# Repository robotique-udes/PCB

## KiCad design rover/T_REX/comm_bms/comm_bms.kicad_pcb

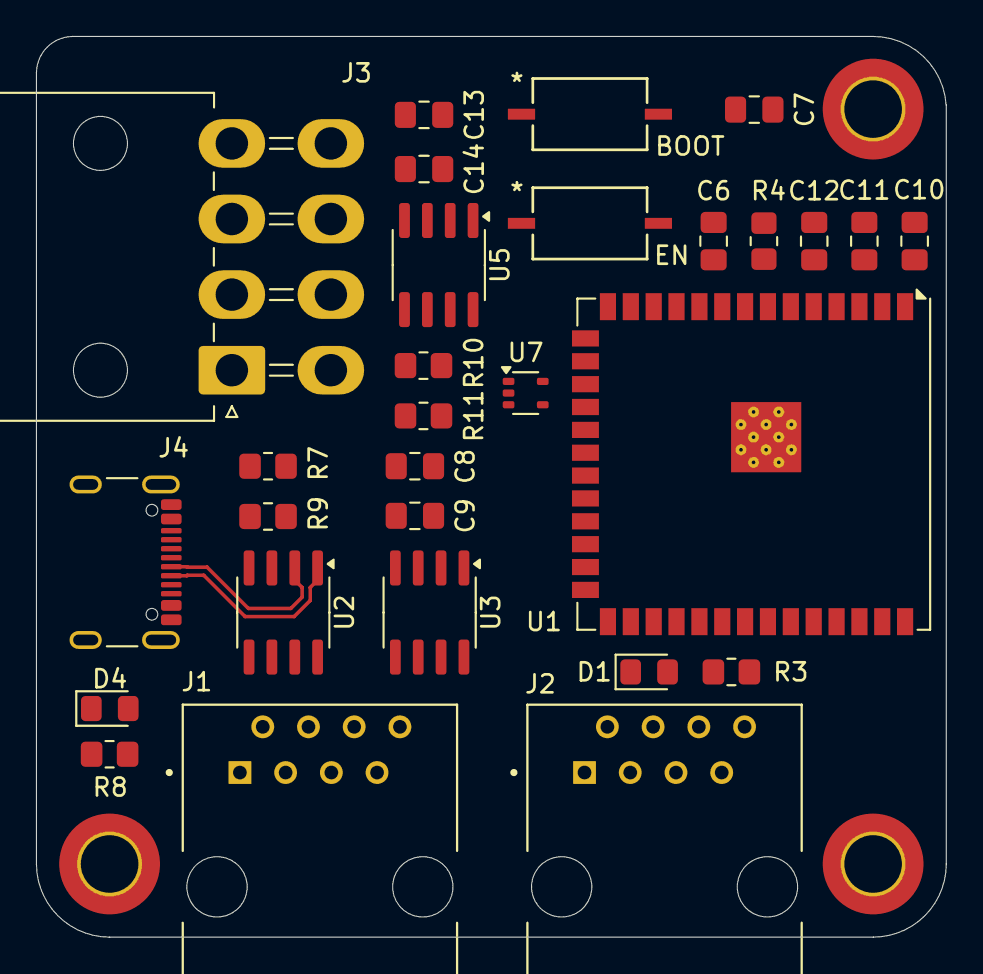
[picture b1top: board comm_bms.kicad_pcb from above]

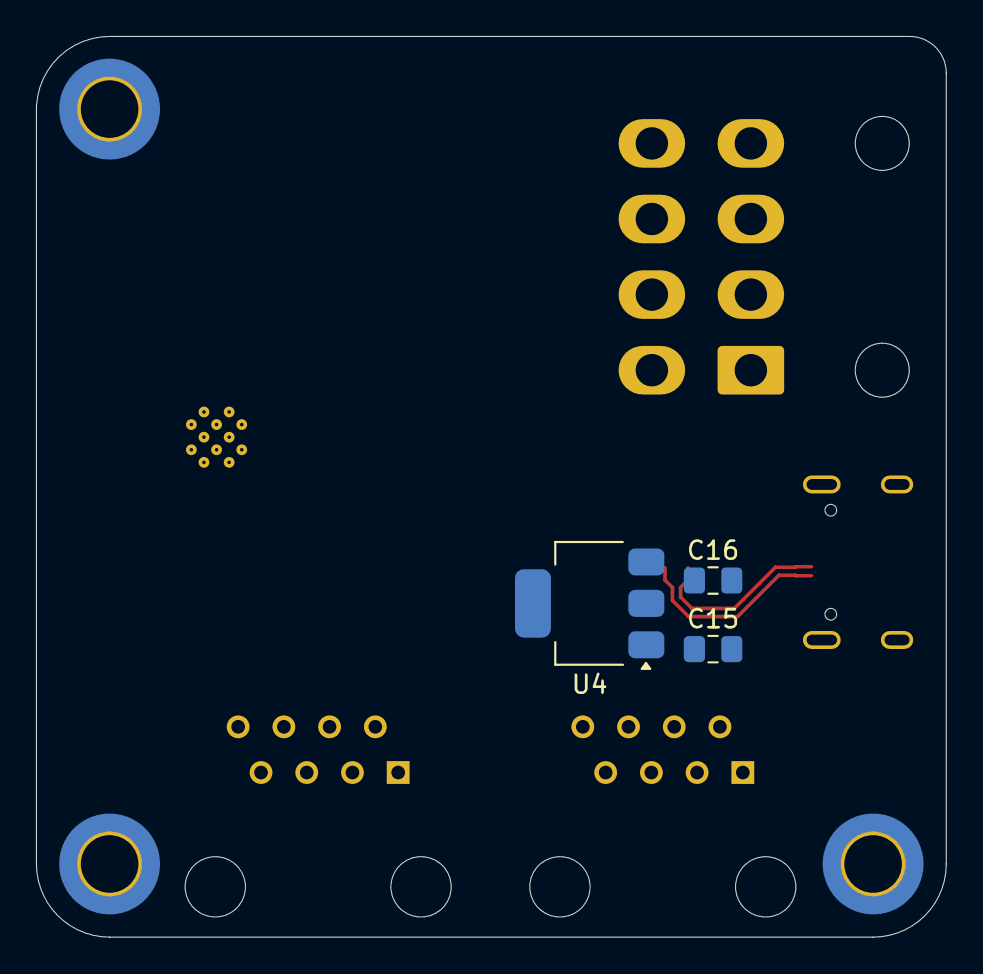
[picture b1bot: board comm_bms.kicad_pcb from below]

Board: 4 copper layers, 50.5 x 50.0 mm, 35 parts (3 on the bottom side), 28 nets.

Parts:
BOOT: TS09-63-25-WT-160-SMT-TR; SW_TS09-63-25_CUD
C6, C7, C9, C11, C14: 100nF; C_0805_2012Metric_Pad1.18x1.45mm_HandSolder
C8, C13, C15: 10uF; C_0805_2012Metric_Pad1.18x1.45mm_HandSolder
C10, C16: 22uF; C_0805_2012Metric_Pad1.18x1.45mm_HandSolder
C12: 1uF; C_0805_2012Metric_Pad1.18x1.45mm_HandSolder
D1: R; LED_0805_2012Metric_Pad1.15x1.40mm_HandSolder
D4: G; LED_0805_2012Metric_Pad1.15x1.40mm_HandSolder
EN: TS09-63-25-WT-160-SMT-TR; SW_TS09-63-25_CUD
H1, H2, H4: MountingHole_Pad; MountingHole_3.2mm_M3_DIN965_Pad_TopBottom
J1, J2: Eth-Horiz-54601-908WPLF; Ethernet_Horizontal
J3: 39301080; Molex_Mini-Fit_Jr_5569-08A2_2x04_P4.20mm_Horizontal
J4: USB_C_USB4105-GF-A; USB_C_Receptacle_GCT_USB4105-xx-A_16P_TopMnt_Horizontal
R3, R8: 1k; R_0805_2012Metric_Pad1.20x1.40mm_HandSolder
R4: 10k; R_0805_2012Metric_Pad1.20x1.40mm_HandSolder
R7, R9: 5k1; R_0805_2012Metric_Pad1.20x1.40mm_HandSolder
R10, R11: 0; R_0805_2012Metric_Pad1.20x1.40mm_HandSolder
U1: ESP32-S3-WROOM-1; ESP32-S3-WROOM-1U
U2: TVS; SOIC-8_3.9x4.9mm_P1.27mm
U3, U5: SN65HVD232Q; SOIC-8_3.9x4.9mm_P1.27mm
U4: LDO-AZ1117CH2-3.3TRG1; SOT-223-3_TabPin2
U7: AXP1T34; SOT-353_SC-70-5

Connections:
5V_USB: J1.5, J1.7, J2.5, J2.7
+3.3V: C8.1, C9.1, C10.1, C11.1, C13.1, C14.1, C16.1, R4.1, R8.2, U1.2 (3V3), U3.3 (VCC), U4.3 (OUTPUT), U5.3 (VCC), U7.5 (Vcco)
+5V_USB: C15.1, J4.A4 (VBUS), J4.A9 (VBUS), J4.B4 (VBUS), J4.B9 (VBUS), R10.1, U2.3, U4.1 (INPUT)
CANH: J1.1 (CANH), J2.1 (CANH), U3.7 (CANH)
CANH_B: J3.1, U5.7 (CANH)
CANL: J1.2 (CANL), J2.2 (CANL), U3.6 (CANL)
CANL_B: J3.2, U5.6 (CANL)
EN_PB: C6.2, C12.1, EN.2, R4.2, U1.3 (EN)
GND: BOOT.1, C6.1, C7.1, C8.2, C9.2, C10.2, C11.2, C12.2, C13.2, C14.2, C15.2, C16.2, D1.1 (K), D4.1 (K), EN.1, H1.1, H2.1, H4.1, J1.6, J1.8, J2.6, J2.8, J3.7, J4.A1 (GND), J4.A12 (GND), J4.B1 (GND), J4.B12 (GND), J4.S1 (SHIELD), R7.2, R9.2, U1.1 (GND), U1.40 (GND), U1.41 (GND), U2.5, U2.6, U2.7, U2.8, U3.2 (GND), U3.8 (S), U4.2 (GND), U5.2 (GND), U5.8 (S), U7.3 (GND)
GPIO_0: BOOT.2, C7.2, U1.27 (IO0-BOOT)
LED_BUILDIN: R3.2, U1.5 (IO5)
unnamed: D1.2 (A), R3.1
unnamed: D4.2 (A), R8.1
unnamed: J1.3, J2.3
unnamed: J1.4, J2.4
unnamed: J4.A5 (CC1), R7.1
unnamed: J4.B5 (CC2), R9.1
unnamed: R11.2, U7.2 (INPUT)
unnamed: R10.2, U7.1 (Vcci)
PWM_3V: U1.33 (IO40), U7.4 (OUTPUT)
PWM_5V: J3.6, R11.1
PWM_EN: J3.8, U1.34 (IO41)
RXB: U1.36 (RXD0), U5.4 (RXD)
RXC: U1.24 (IO47), U3.4 (RXD)
TXB: U1.37 (TXD0), U5.1 (TXD)
TXC: U1.25 (IO48), U3.1 (TXD)
USB_N: J4.A7 (D-), J4.B7 (D-), U1.13 (IO19-USB_N), U2.2
USB_P: J4.A6 (D+), J4.B6 (D+), U1.14 (IO20-USB-P), U2.1

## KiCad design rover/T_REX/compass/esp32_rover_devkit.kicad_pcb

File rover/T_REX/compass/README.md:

# Antenna
PCB servant de module de centrale inertielle et de boussole

Voici les informations concernant le PCB : Compass

## Image du PCB en 3D

## Objectifs:
* Permettre au Rover d'avoir des information sur sa position et son orientation dans l'espace
* 

## Composants principaux:
* ESP32-S3-WROOM-1
* TJA1050T (CAN BUS)
* WT901 (compass)
* Ports Ethernets
* AZ1117ID-3.3 (LDO)
* TVS diodes

## Fonctionnement:
Le MCU peut lire les données de la centrale inertielle et boussole par UART.
Le MCU peut transmettre les informations du senseur par le CAN bus.
Le CAN bus peut passer à travers le circuit, donc un autre circuit peut être branché à la suite de celui-ci.

## PGIO
### Outputs

Name         | GPIO
---          | ---
LED_BUILDIN  | D2
STEPPIN      | D37
DIRPIN       | D38
ENABLEPIN    | D39

### Communication

Name    | GPIO
---     | ---
USBN    | D19
USBP    | D20
SCL     | D21
SDA     | D09
TX_WT   | D13
RX_WT   | D12
TXC     | D48
RXC     | D47

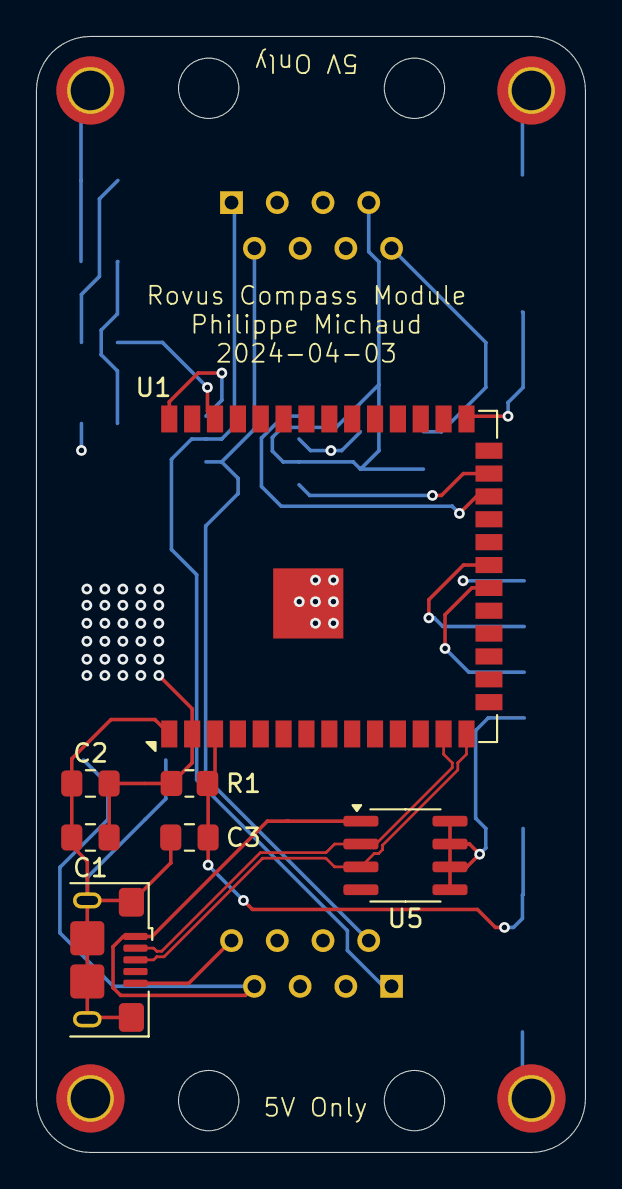
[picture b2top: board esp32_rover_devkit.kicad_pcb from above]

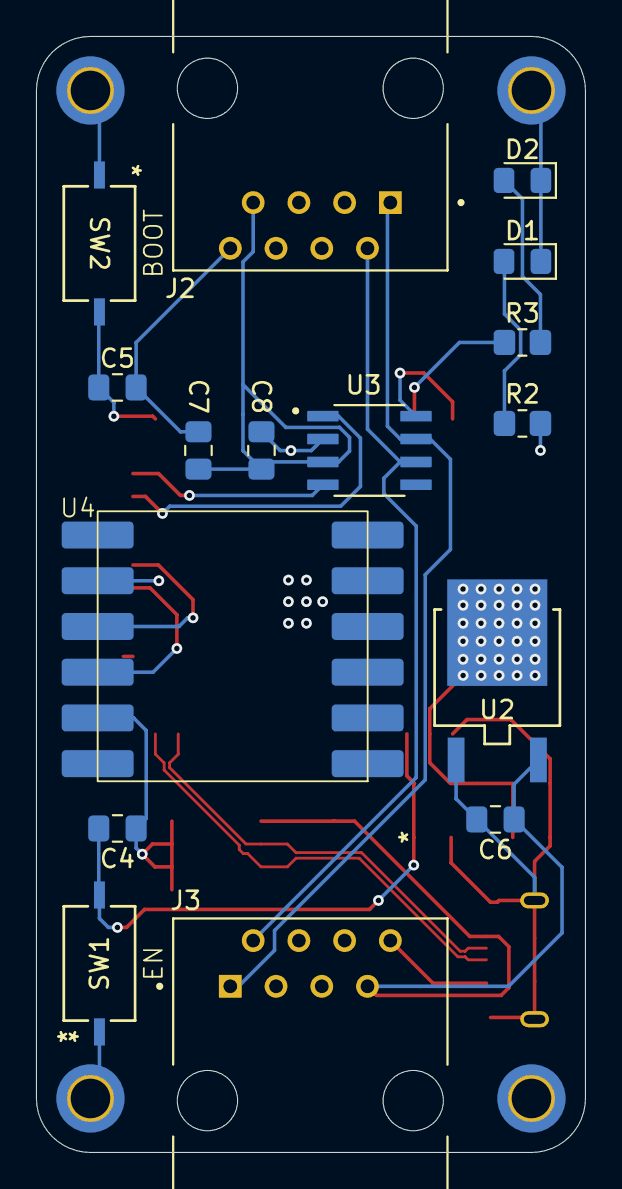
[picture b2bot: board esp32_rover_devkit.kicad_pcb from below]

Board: 4 copper layers, 30.5 x 62.0 mm, 27 parts (16 on the bottom side), 16 nets.

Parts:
C1: 22uF; C_0805_2012Metric_Pad1.18x1.45mm_HandSolder
C2, C4, C5, C8: 100nF; C_0805_2012Metric_Pad1.18x1.45mm_HandSolder
C3: 1uF; C_0805_2012Metric_Pad1.18x1.45mm_HandSolder
C6, C7: 10uF; C_0805_2012Metric_Pad1.18x1.45mm_HandSolder
D1, D2: R; LED_0805_2012Metric_Pad1.15x1.40mm_HandSolder
H1, H2, H3, H4: MountingHole_Pad; MountingHole_2.2mm_M2_DIN965_Pad_TopBottom
J1: USB_B_Micro; USB_Micro-B_Amphenol_10118193-0001LF_Horizontal
J2, J3: RJ45; AMPHENOL_54601-908WPLF
R1: 10K TBV; R_0805_2012Metric_Pad1.20x1.40mm_HandSolder
R2, R3: 1k; R_0805_2012Metric_Pad1.20x1.40mm_HandSolder
SW1, SW2: TS09-63-25-WT-160-SMT-TR; SW_TS09-63-25_CUD
U1: ESP32-S3-WROOM-1
U2: AZ1117ID-3.3TRG1; TO252-2_AZ1117ID-3.3TRG1_DIO
U3: TJA1050T_CM_118; SOIC127P600X175-8N
U4: WT910C
U5: SOIC-8-1EP_3.9x4.9mm_P1.27mm_EP2.29x3mm

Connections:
+3.3V: C1.1, C2.1, R1.1, R2.2, U1.2 (3V3), U2.2 (OUTPUT), U4.2 (Vcc)
+5V: C6.1, C7.1, C8.1, J1.1 (VBUS), J2.7, J3.7, U2.3 (INPUT), U3.3 (VCC), U5.1
CANH: J2.1, J3.1, U3.7 (CANH)
CANL: J2.2, J3.2, U3.6 (CANL)
EN_PB: C3.1, C4.2, R1.2, SW1.2, U1.3 (EN)
GND: C1.2, C2.2, C3.2, C4.1, C5.1, C6.2, C7.2, C8.2, D1.1 (K), D2.1 (K), H1.1, H2.1, H3.1, H4.1, J1.5 (GND), J1.6 (Shield), J2.8, J3.8, SW1.1, SW2.1, U1.1 (GND), U1.40 (GND), U1.41 (GND), U2.1 (GND), U3.2 (GND), U3.8 (S), U4.5 (GND), U5.5, U5.6, U5.7, U5.8
GPIO_0: C5.2, SW2.2, U1.27 (IO0)
LED_BUILDIN: R3.2, U1.38 (IO2)
unnamed: D1.2 (A), R2.1
unnamed: D2.2 (A), R3.1
RX1: U1.20 (IO12), U4.4 (TX)
RXC: U1.24 (IO47), U3.1 (TXD)
TX1: U1.21 (IO13), U4.3 (RX)
TXC: U1.25 (IO48), U3.4 (RXD)
USB_N: J1.2 (D-), U1.13 (IO19), U5.2
USB_P: J1.3 (D+), U1.14 (IO20), U5.3

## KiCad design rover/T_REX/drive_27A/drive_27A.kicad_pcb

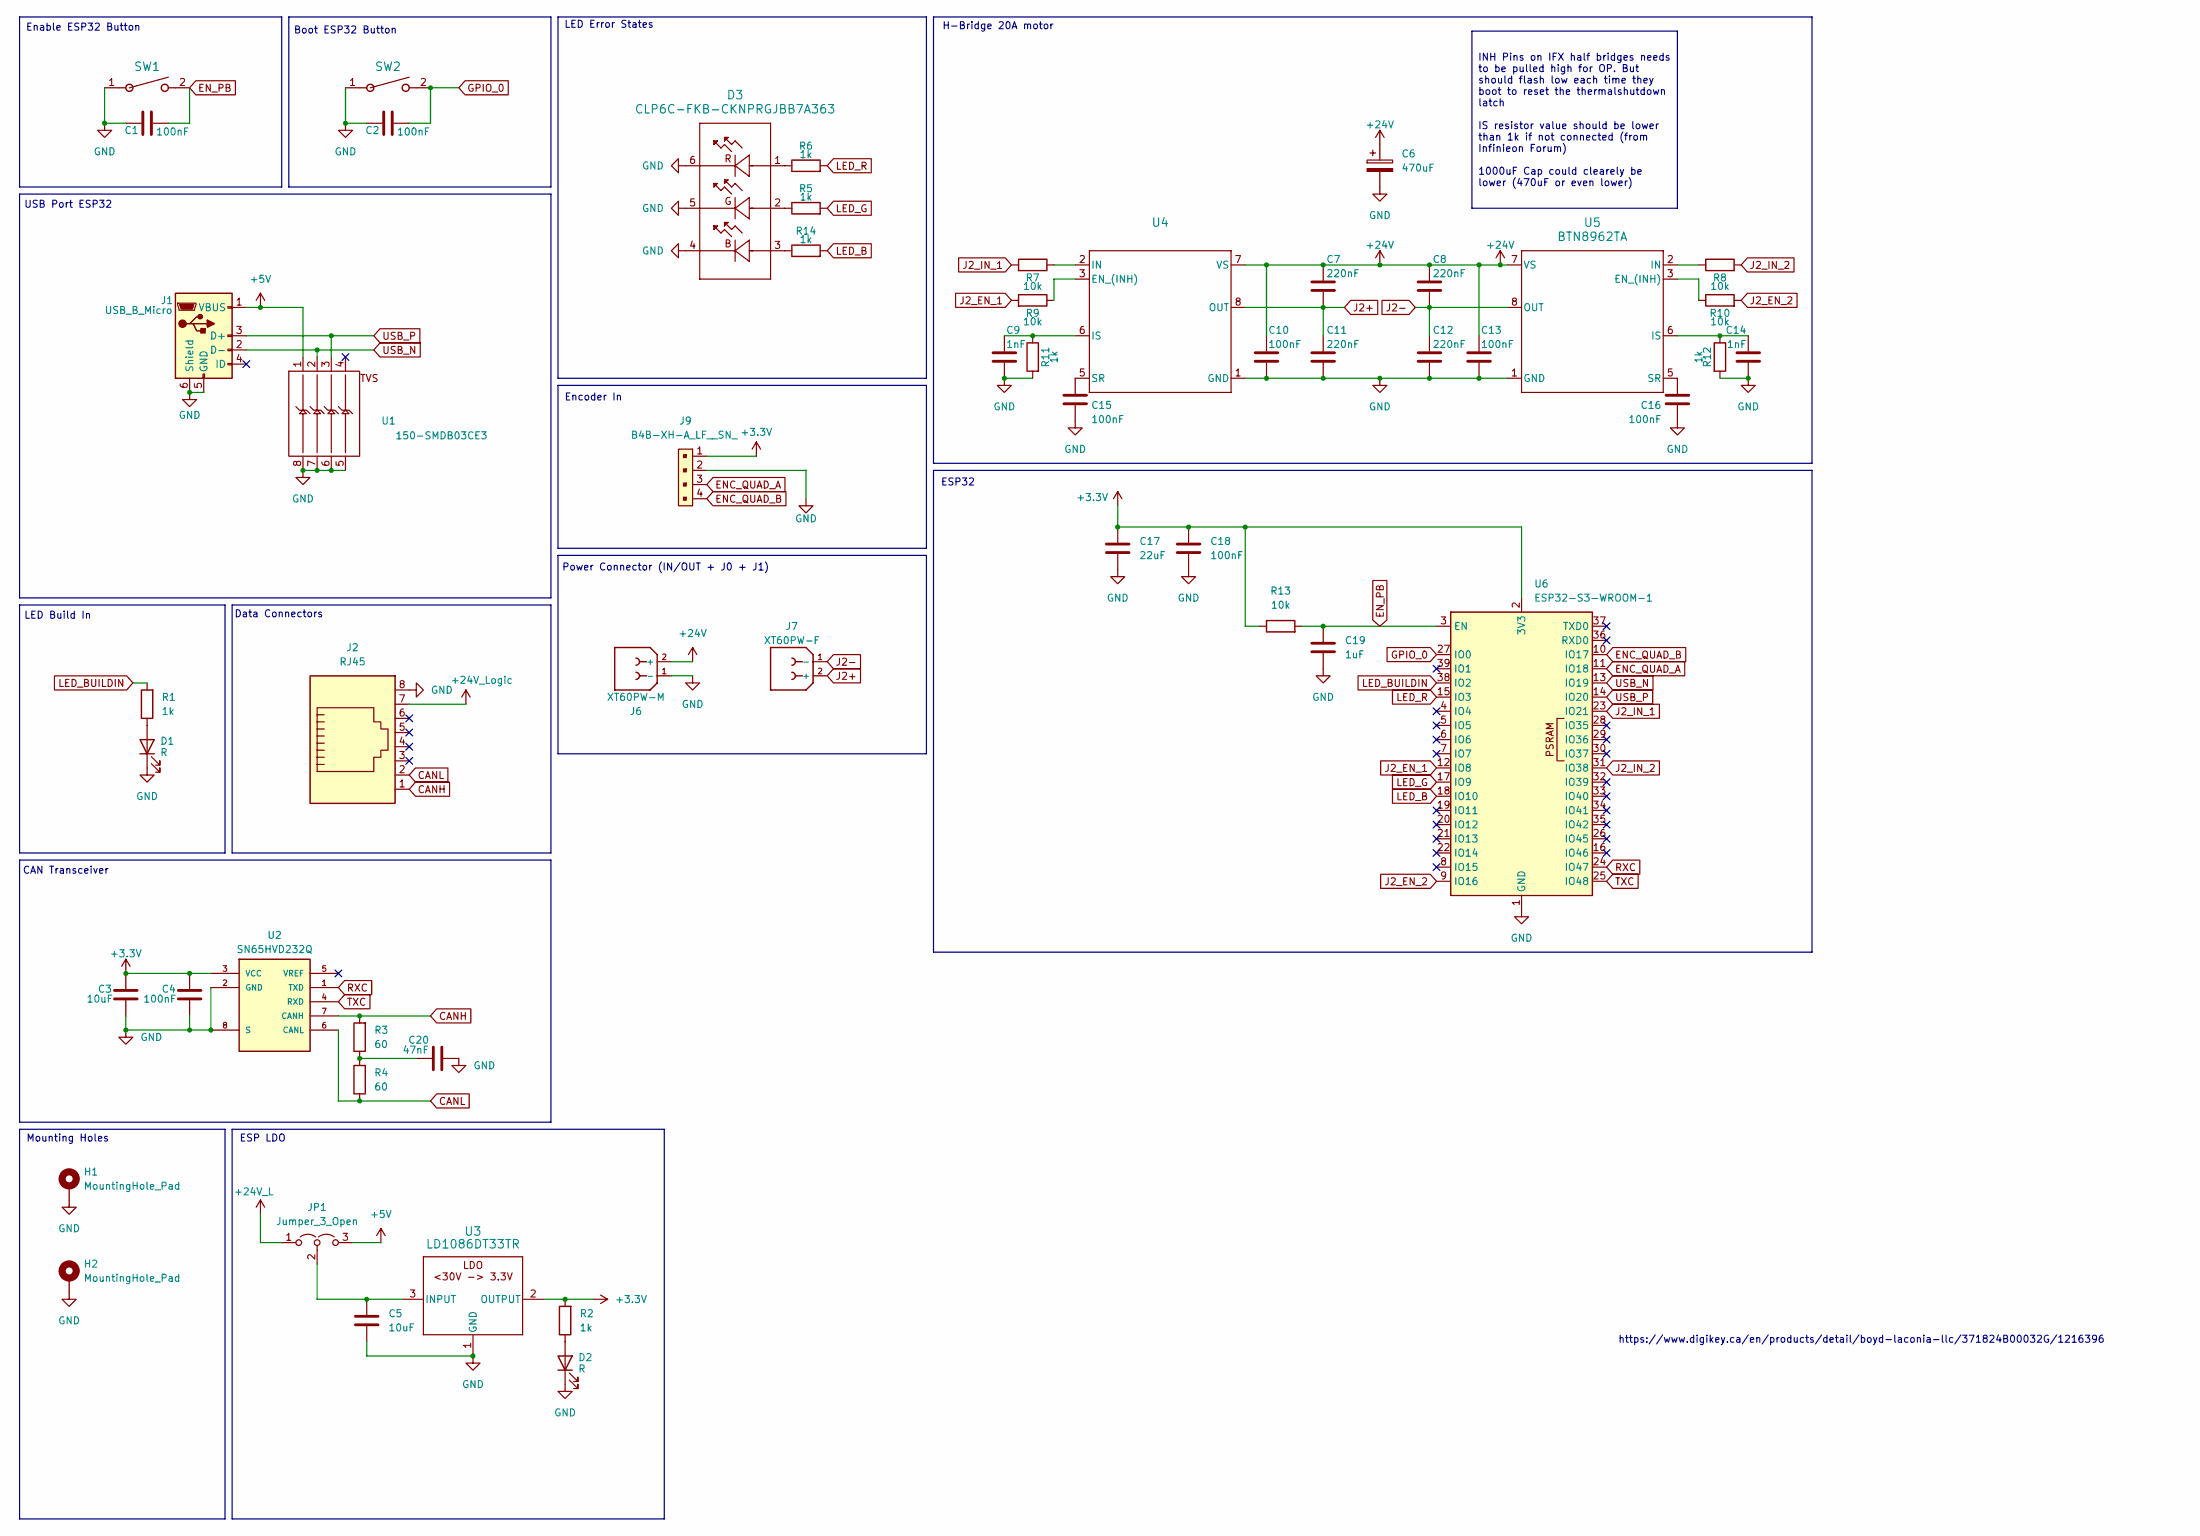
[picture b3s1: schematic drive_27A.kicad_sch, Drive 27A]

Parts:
C1, C2, C4, C10, C13, C15, C16, C18: 100nF; C_0805_2012Metric_Pad1.18x1.45mm_HandSolder; LCSC C111492
C3, C5: 10uF; C_0805_2012Metric_Pad1.18x1.45mm_HandSolder; LCSC C440198
C6: 470uF; CP_Radial_D12.5mm_P5.00mm; LCSC C165494
C7, C8, C11, C12: 220nF; C_0805_2012Metric_Pad1.18x1.45mm_HandSolder; LCSC C86042
C9, C14: 1nF; C_0805_2012Metric_Pad1.18x1.45mm_HandSolder; LCSC C46553
C17: 22uF; C_0805_2012Metric_Pad1.18x1.45mm_HandSolder; LCSC C76634
C19: 1uF; C_0805_2012Metric_Pad1.18x1.45mm_HandSolder; LCSC C77079
C20: 47nF; C_0805_2012Metric_Pad1.18x1.45mm_HandSolder; LCSC C1777
D1, D2: R; LED_0805_2012Metric_Pad1.15x1.40mm_HandSolder; LCSC C19171391
D3: CLP6C-FKB-CKNPRGJBB7A363; CLP6C-FKB-CKNPRGJBB7A363_CRE; LCSC C7107714
H1, H2: MountingHole_Pad; MountingHole_3.2mm_M3_DIN965_Pad_TopBottom
J1: USB_B_Micro; USB_Micro-B_Amphenol_10118193-0001LF_Horizontal; LCSC C132562
J2: RJ45; AMPHENOL_54601-908WPLF; LCSC C598568
J6: XT60PW-M; AMASS_XT60PW-M_1x02_P7.20mm_Horizontal; LCSC C98732
J7: XT60PW-F; AMASS_XT60PW-F_1x02_P7.20mm_Horizontal; LCSC C428722
J9: B4B-XH-A_LF__SN_; JST_PH_B4B-PH-SM4-TB_1x04-1MP_P2.00mm_Vertical; MPN B4B-XH-A(LF)(SN); LCSC C157999
JP1: Jumper_3_Open; PinHeader_1x03_P2.54mm_Vertical
R1, R2, R5, R6, R11, R12, R14: 1k; R_0805_2012Metric_Pad1.20x1.40mm_HandSolder; LCSC C75245
R3, R4: 60; R_0805_2012Metric_Pad1.20x1.40mm_HandSolder; LCSC C2767521
R7, R8, R9, R10, R13: 10k; R_0805_2012Metric_Pad1.20x1.40mm_HandSolder; LCSC C25612
SW1, SW2: TS09-63-25-WT-160-SMT-TR; SW_TS09-63-25_CUD; LCSC C455236
U1: 150-SMDB03CE3; SOIC-8-1EP_3.9x4.9mm_P1.27mm_EP2.29x3mm; LCSC C1973174
U2: SN65HVD232Q; SOIC127P600X175-8N; PARTREV 4; LCSC C130019
U3: LD1086DT33TR; TO252-2_AZ1117ID-3.3TRG1_DIO-L; LCSC C12051
U4, U5: BTN8962TA; PG-TO263-7-1_INF-M; LCSC C534738
U6: ESP32-S3-WROOM-1; LCSC C2980297

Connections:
+3.3V: C3.1, C4.1, C17.1, C18.1, J9.1, R2.2, R13.1, U2.3 (VCC), U3.2 (OUTPUT), U6.2 (3V3)
+5V: J1.1 (VBUS), JP1.3 (B), U1.1
+24V: C6.1, C7.1, C8.1, C10.1, C13.1, J6.2 (+), U4.7 (VS), U5.7 (VS)
CANH: J2.1, R3.2, U2.7 (CANH)
CANL: J2.2, R4.1, U2.6 (CANL)
ENC_QUAD_A: J9.3, U6.11 (IO18)
ENC_QUAD_B: J9.4, U6.10 (IO17)
EN_PB: C1.2, C19.1, R13.2, SW1.2, U6.3 (EN)
GND: C1.1, C2.1, C3.2, C4.2, C5.2, C6.2, C9.2, C10.2, C11.2, C12.2, C13.2, C14.2, C15.2, C16.2, C17.2, C18.2, C19.2, C20.1, D1.1 (K), D2.1 (K), D3.4, D3.5, D3.6, H1.1, H2.1, J1.5 (GND), J1.6 (Shield), J2.8, J6.1 (-), J9.2, R11.2, R12.2, SW1.1, SW2.1, U1.5, U1.6, U1.7, U1.8, U2.2 (GND), U2.8 (S), U3.1 (GND), U4.1 (GND), U5.1 (GND), U6.1 (GND), U6.40 (GND), U6.41 (GND)
GPIO_0: C2.2, SW2.2, U6.27 (IO0)
J2+: C7.2, C11.1, J7.2 (+), U4.8 (OUT)
J2-: C8.2, C12.1, J7.1 (-), U5.8 (OUT)
J2_EN_1: R9.2, U6.12 (IO8)
J2_EN_2: R10.2, U6.9 (IO16)
J2_IN_1: R7.2, U6.23 (IO21)
J2_IN_2: R8.2, U6.31 (IO38)
LED_B: R14.2, U6.18 (IO10)
LED_BUILDIN: R1.2, U6.38 (IO2)
LED_G: R5.2, U6.17 (IO9)
LED_R: R6.2, U6.15 (IO3)
unnamed: C20.2, R3.1, R4.2
unnamed: D1.2 (A), R1.1
unnamed: D2.2 (A), R2.1
unnamed: D3.1, R6.1
unnamed: D3.2, R5.1
unnamed: D3.3, R14.1
unnamed: C5.1, JP1.2 (C), U3.3 (INPUT)
unnamed: R9.1, U4.3 (EN_(INH))
unnamed: R7.1, U4.2 (IN)
unnamed: C9.1, R11.1, U4.6 (IS)
unnamed: C15.1, U4.5 (SR)
unnamed: R10.1, U5.3 (EN_(INH))
unnamed: R8.1, U5.2 (IN)
unnamed: C14.1, R12.1, U5.6 (IS)
unnamed: C16.1, U5.5 (SR)
RXC: U2.1 (TXD), U6.24 (IO47)
TXC: U2.4 (RXD), U6.25 (IO48)
USB_N: J1.2 (D-), U1.2, U6.13 (IO19)
USB_P: J1.3 (D+), U1.3, U6.14 (IO20)

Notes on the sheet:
INH Pins on IFX half bridges needs to be pulled high for OP. But should flash low each time they boot to reset the thermalshutdown latch IS resistor value should be lower than 1k if not connected (from Infinieon Forum) 1000uF Cap could clearely be lower (470uF or even lower)
Boot ESP32 Button
LED Build In
Enable ESP32 Button
CAN Transceiver
Encoder In
LED Error States
Power Connector (IN/OUT + J0 + J1)
ESP LDO
Data Connectors
H-Bridge 20A motor
Mounting Holes
USB Port ESP32
https://www.digikey.ca/en/products/detail/boyd-laconia-llc/371824B00032G/1216396
ESP32

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
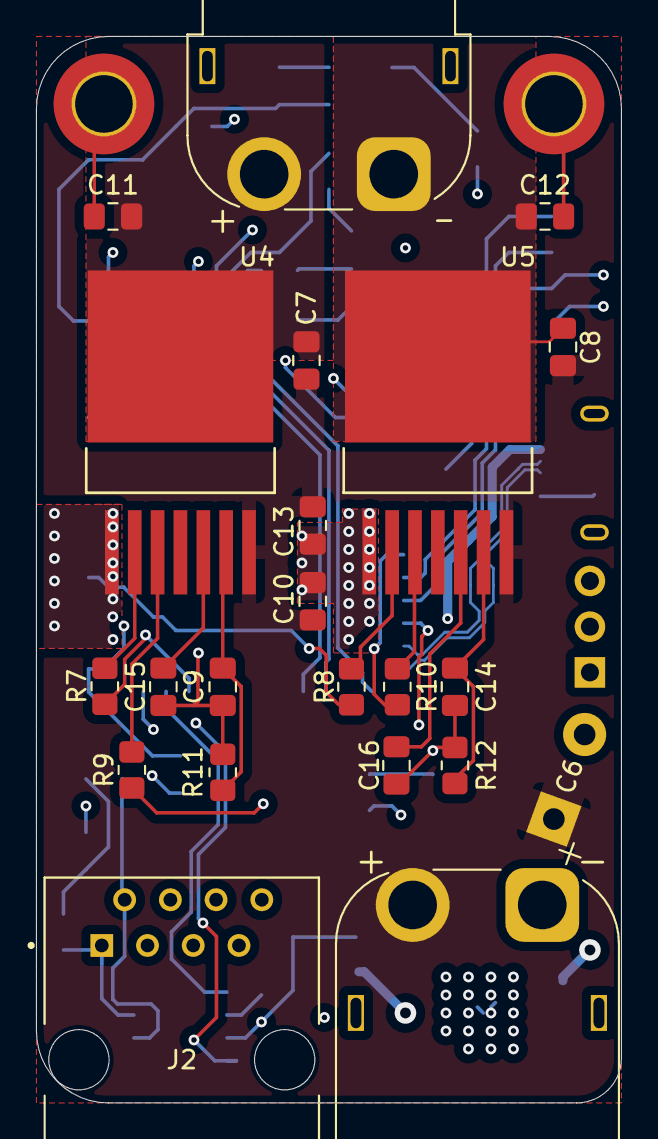
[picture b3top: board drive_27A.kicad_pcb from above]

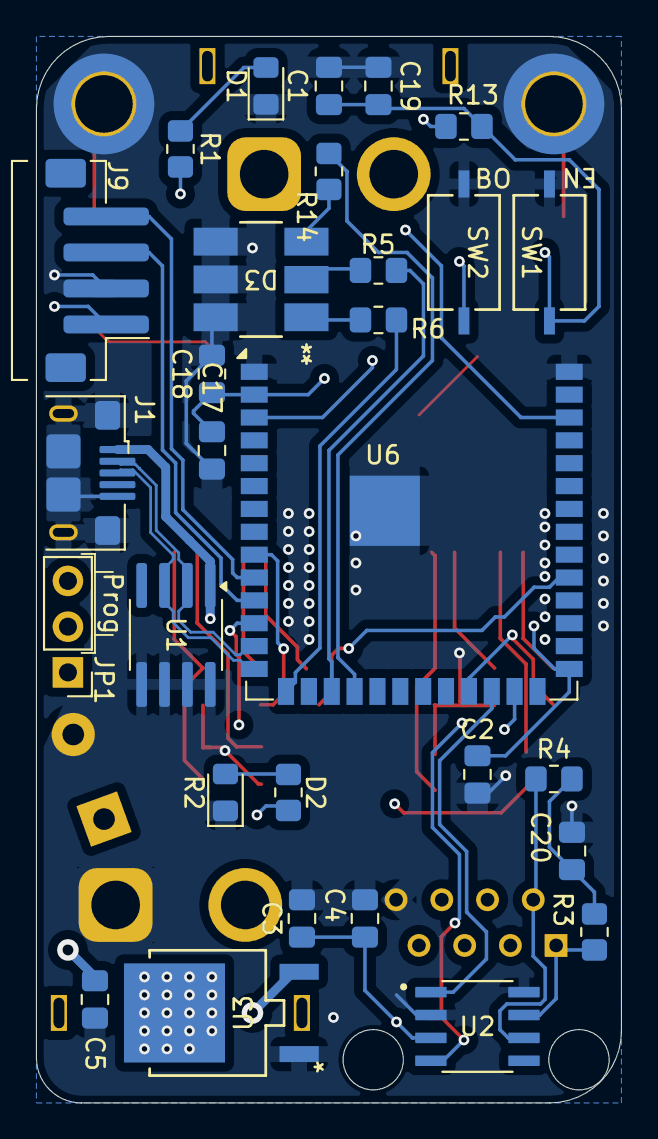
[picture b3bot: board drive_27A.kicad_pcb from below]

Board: 4 copper layers, 32.5 x 59.3 mm, 53 parts (29 on the bottom side), 40 nets.

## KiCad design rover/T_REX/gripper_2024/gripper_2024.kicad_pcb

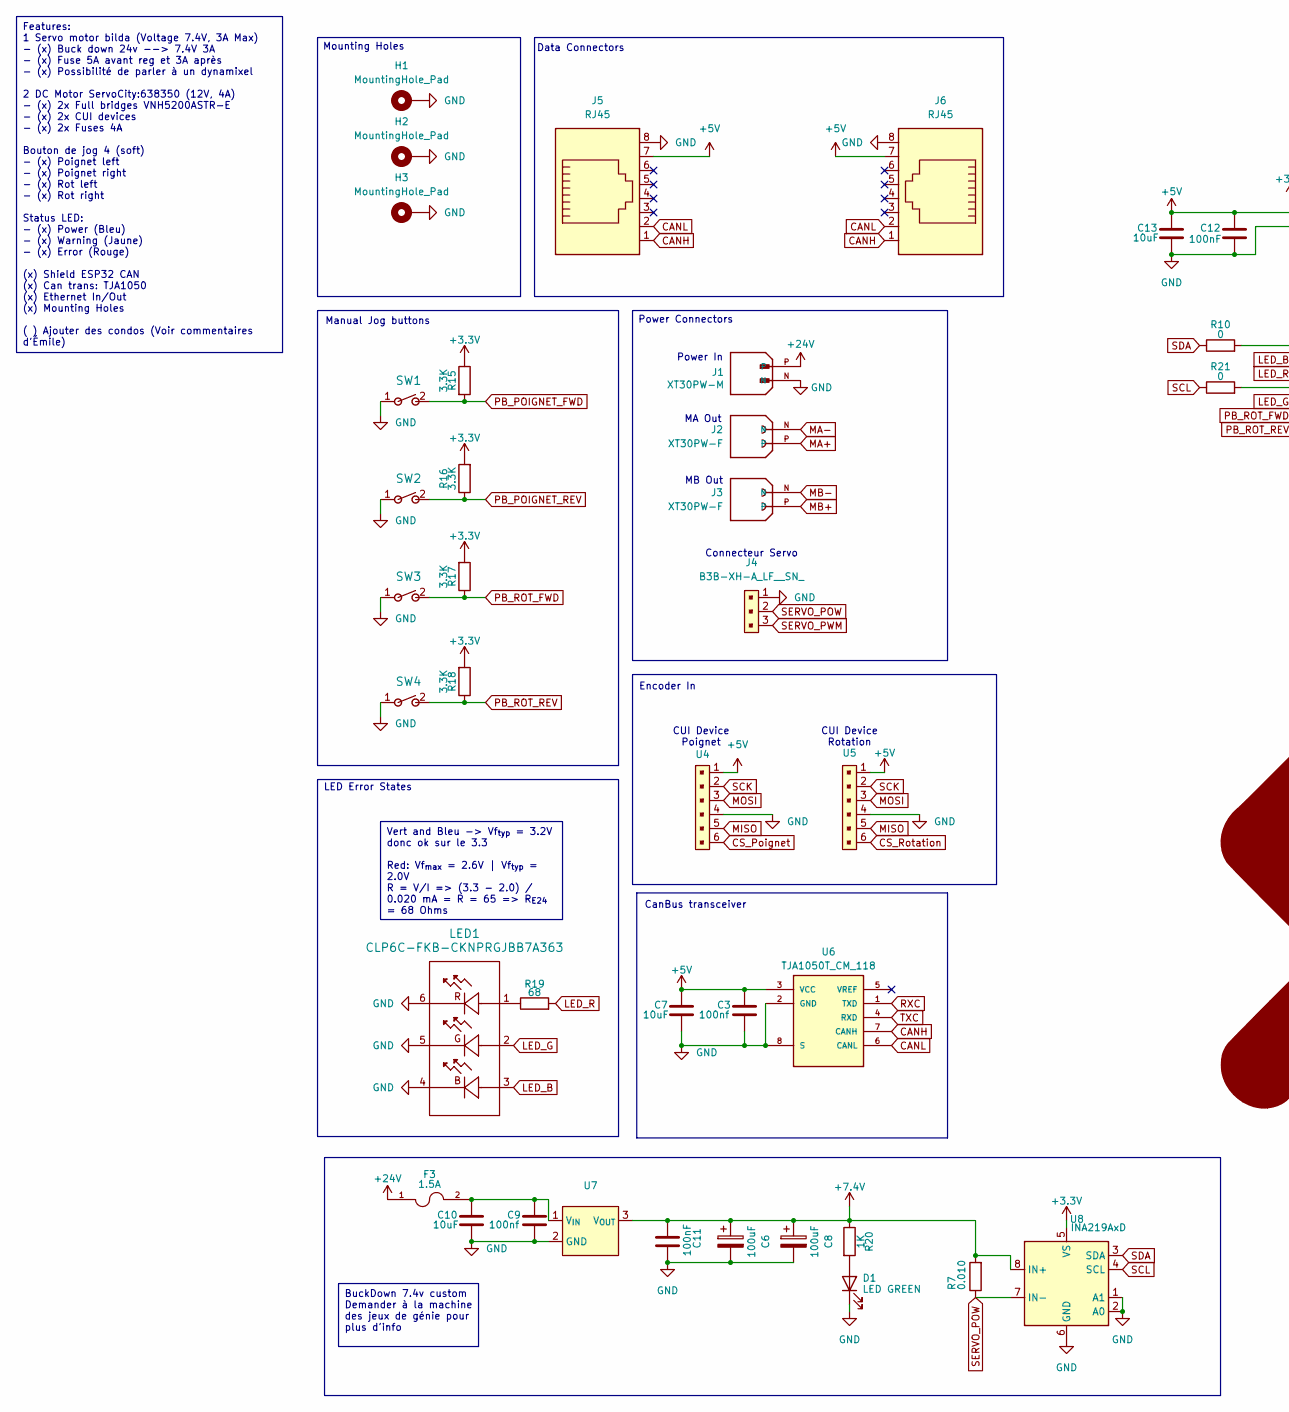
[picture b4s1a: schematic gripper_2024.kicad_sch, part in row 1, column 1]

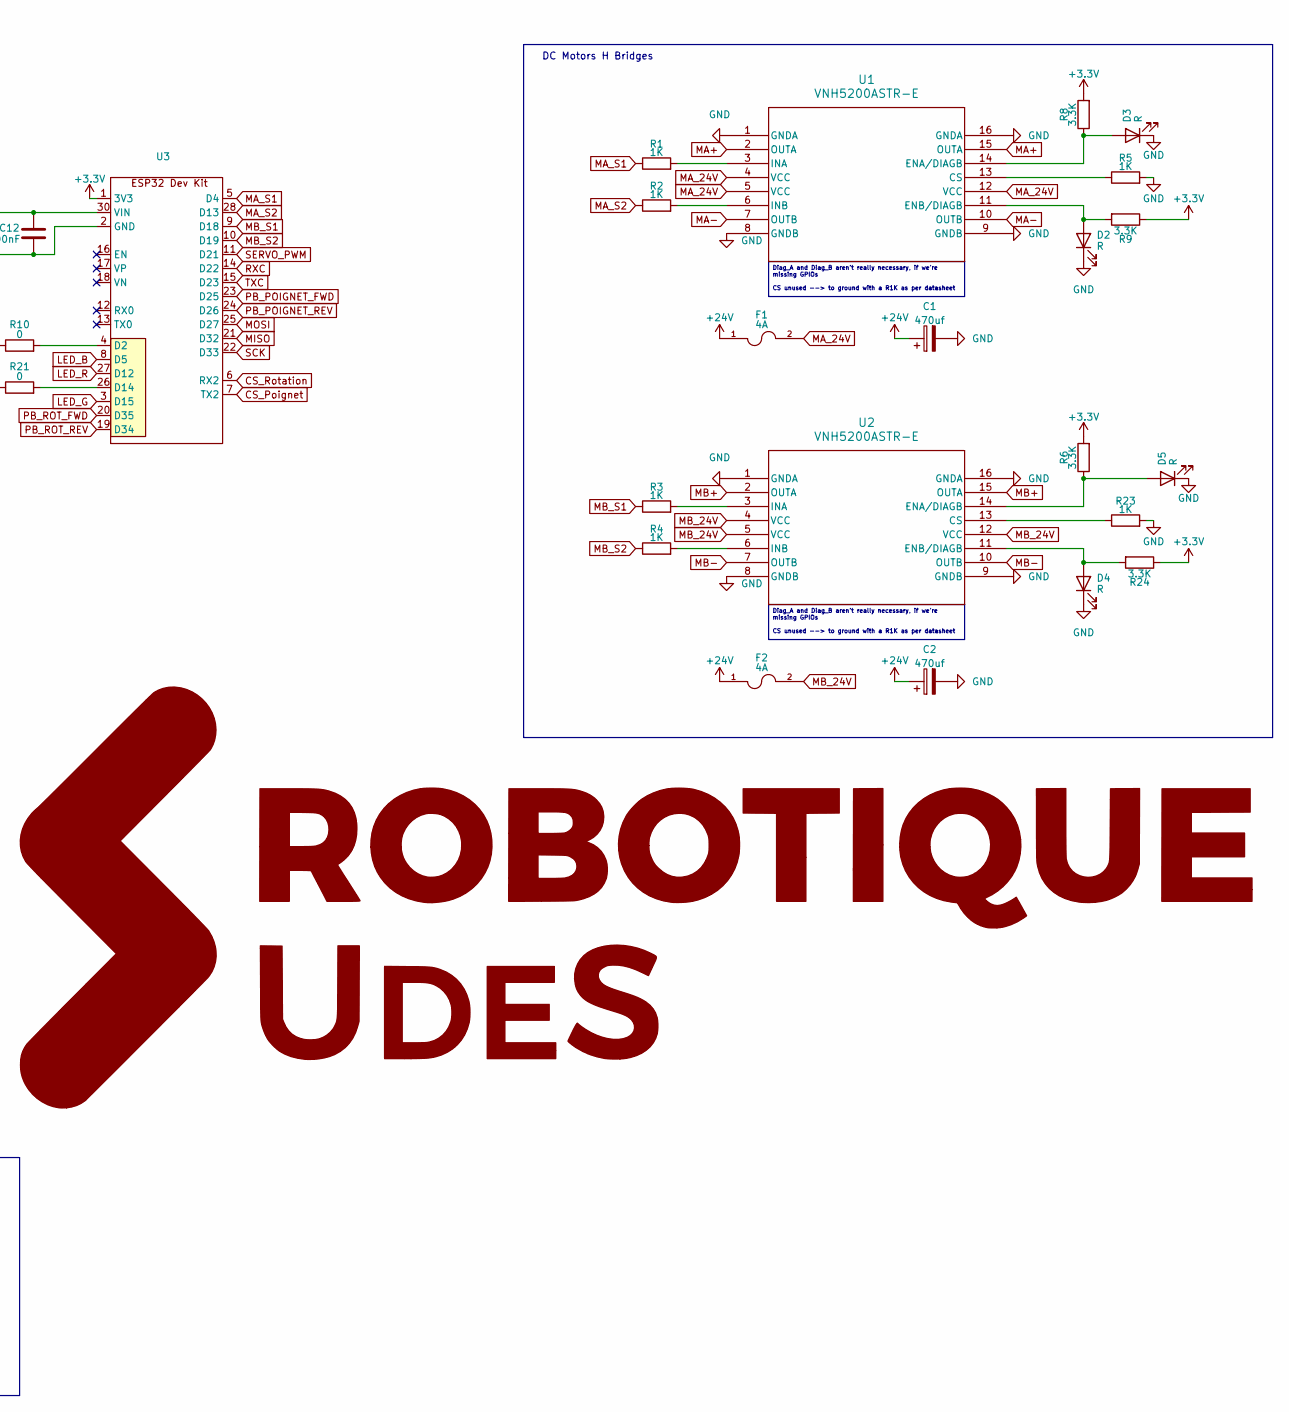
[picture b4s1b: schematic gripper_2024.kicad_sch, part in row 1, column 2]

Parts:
C1, C2: 470uf; CP_Radial_D10.0mm_P5.00mm
C3, C9: 100nf; C_0805_2012Metric_Pad1.18x1.45mm_HandSolder
C6, C8: 100uF; CP_Radial_D5.0mm_P2.00mm
C7, C10, C13: 10uF; C_0805_2012Metric_Pad1.18x1.45mm_HandSolder
C11, C12: 100nF; C_0805_2012Metric_Pad1.18x1.45mm_HandSolder
D1: LED GREEN; LED_0805_2012Metric_Pad1.15x1.40mm_HandSolder
D2, D3, D4, D5: R; LED_0805_2012Metric_Pad1.15x1.40mm_HandSolder
F1, F2: 4A; 3425L200_60MR
F3: 1.5A; Fuse_1812_4532Metric_Pad1.30x3.40mm_HandSolder
H1, H2, H3: MountingHole_Pad; MountingHole_3.2mm_M3_DIN965_Pad_TopBottom
J1: XT30PW-M; AMASS_XT30PW-M; PARTREV 1.2
J2, J3: XT30PW-F; AMASS_XT30PW-F; PARTREV 1.2
J4: B3B-XH-A_LF__SN_; JST_XH_B3B-XH-AM_1x03_P2.50mm_Vertical; MPN B3B-XH-A(LF)(SN)
J5, J6: RJ45; AMPHENOL_54601-908WPLF
LED1: CLP6C-FKB-CKNPRGJBB7A363; CLP6C-FKB-CKNPRGJBB7A363_CRE
R1, R2, R3, R4, R5, R20, R23: 1K; R_0805_2012Metric_Pad1.20x1.40mm_HandSolder
R6, R8, R9, R15, R16, R17, R18, R24: 3.3K; R_0805_2012Metric_Pad1.20x1.40mm_HandSolder
R7: 0.010; R_1206_3216Metric_Pad1.30x1.75mm_HandSolder
R10, R21: 0; R_0805_2012Metric_Pad1.20x1.40mm_HandSolder
R19: 68; R_0805_2012Metric_Pad1.20x1.40mm_HandSolder
SW1, SW2, SW3, SW4: TS09-63-25-WT-160-SMT-TR; SW_TS09-63-25_CUD
U1, U2: VNH5200ASTR-E; SO_200AS-E_STM
U3: MODULE_ESP32_DEVKIT_V1
U4, U5: JST_XH_B6B-XH-AM_1x06_P2.50mm_Vertical
U6: TJA1050T_CM_118; SOIC127P600X175-8N; PARTREV 4
U7: REG_7.4V
U8: INA219AxD; SOIC-8_3.9x4.9mm_P1.27mm

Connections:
+3.3V: R6.2, R8.2, R9.1, R15.1, R16.2, R17.2, R18.2, R24.1, U3.1 (3V3), U8.5 (VS)
+5V: C3.1, C7.1, C12.1, C13.1, J5.7, J6.7, U3.30 (VIN), U4.1, U5.1, U6.3 (VCC)
+7.4V: C6.1, C8.1, C11.2, R7.2, R20.1, U7.3 (V_{OUT}), U8.8 (IN+)
+24V: C1.1, C2.1, F1.1, F2.1, F3.1, J1.P
CANH: J5.1, J6.1, U6.7 (CANH)
CANL: J5.2, J6.2, U6.6 (CANL)
CS_Poignet: U3.7 (TX2), U4.6
CS_Rotation: U3.6 (RX2), U5.6
GND: C1.2, C2.2, C3.2, C6.2, C7.2, C8.2, C9.2, C10.2, C11.1, C12.2, C13.2, D1.1 (K), D2.1 (K), D3.1 (K), D4.1 (K), D5.1 (K), H1.1, H2.1, H3.1, J1.N, J4.1, J5.8, J6.8, LED1.4, LED1.5, LED1.6, R5.2, R23.2, SW1.1, SW2.1, SW3.1, SW4.1, U1.1 (GNDA), U1.8 (GNDB), U1.9 (GNDB), U1.16 (GNDA), U2.1 (GNDA), U2.8 (GNDB), U2.9 (GNDB), U2.16 (GNDA), U3.2 (GND), U4.4, U5.4, U6.2 (GND), U6.8 (S), U7.2 (GND), U8.1 (A1), U8.2 (A0), U8.6 (GND); also elsewhere on the board
LED_B: LED1.3, U3.8 (D5); also elsewhere on the board
LED_G: LED1.2, U3.3 (D15); also elsewhere on the board
LED_R: R19.2, U3.27 (D12)
MA+: J2.P, U1.2 (OUTA), U1.15 (OUTA)
MA-: J2.N, U1.7 (OUTB), U1.10 (OUTB)
MA_24V: F1.2, U1.4 (VCC), U1.5 (VCC), U1.12 (VCC)
MA_S1: R1.1, U3.5 (D4)
MA_S2: R2.1, U3.28 (D13)
MB+: J3.P, U2.2 (OUTA), U2.15 (OUTA)
MB-: J3.N, U2.7 (OUTB), U2.10 (OUTB)
MB_24V: F2.2, U2.4 (VCC), U2.5 (VCC), U2.12 (VCC)
MB_S1: R3.1, U3.9 (D18)
MB_S2: R4.1, U3.10 (D19)
MISO: U3.21 (D32), U4.5, U5.5
MOSI: U3.25 (D27), U4.3, U5.3
unnamed: D1.2 (A), R20.2
unnamed: D2.2 (A), R9.2, U1.11 (ENB/DIAGB)
unnamed: D3.2 (A), R8.1, U1.14 (ENA/DIAGB)
unnamed: D4.2 (A), R24.2, U2.11 (ENB/DIAGB)
unnamed: D5.2 (A), R6.1, U2.14 (ENA/DIAGB)
unnamed 29: LED1.1, R19.1; also elsewhere on the board
unnamed: R5.1, U1.13 (CS)
unnamed: R1.2, U1.3 (INA)
unnamed: R2.2, U1.6 (INB)
unnamed: R23.1, U2.13 (CS)
unnamed: R3.2, U2.3 (INA)
unnamed: R4.2, U2.6 (INB)
unnamed: R10.2, U3.4 (D2)
unnamed: R21.2, U3.26 (D14)
unnamed: C9.1, C10.1, F3.2, U7.1 (V_{IN})
PB_POIGNET_FWD: R15.2, SW1.2, U3.23 (D25)
PB_POIGNET_REV: R16.1, SW2.2, U3.24 (D26)
PB_ROT_FWD: R17.1, SW3.2, U3.20 (D35)
PB_ROT_REV: R18.1, SW4.2, U3.19 (D34)
RXC: U3.14 (D22), U6.1 (TXD)
SCK: U3.22 (D33), U4.2, U5.2
SCL: R21.1, U8.4 (SCL)
SDA: R10.1, U8.3 (SDA)
SERVO_POW: J4.2, R7.1, U8.7 (IN-)
SERVO_PWM: J4.3, U3.11 (D21)
TXC: U3.15 (D23), U6.4 (RXD)

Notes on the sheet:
Vert and Bleu -> Vf_{typ} = 3.2V donc ok sur le 3.3 Red: Vf_{max} = 2.6V | Vf_{typ} = 2.0V R = V/I => (3.3 - 2.0) / 0.020 mA = R = 65 => R_{E24} = 68 Ohms
Features: 1 Servo motor bilda (Voltage 7.4V, 3A Max) - (x) Buck down 24v --> 7.4V 3A - (x) Fuse 5A avant reg et 3A après - (x) Possibilité de parler à un dynamixel 2 DC Motor ServoCity:638350 (12V, 4A) - (x) 2x Full bridges VNH5200ASTR-E - (x) 2x CUI devices - (x) 2x Fuses 4A Bouton de jog 4 (soft)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
BuckDown 7.4v custom Demander à la machine des jeux de génie pour plus d'info
Diag_A and Diag_B aren't really necessary, if we're missing GPIOs CS unused --> to ground with a R1K as per datasheet
Data Connectors
CanBus transceiver
Connecteur Servo
LED Error States
Manual Jog buttons
Power In
MB Out
CUI Device Rotation
DC Motors H Bridges
CUI Device Poignet
MA Out
Encoder In
Power Connectors
Mounting Holes

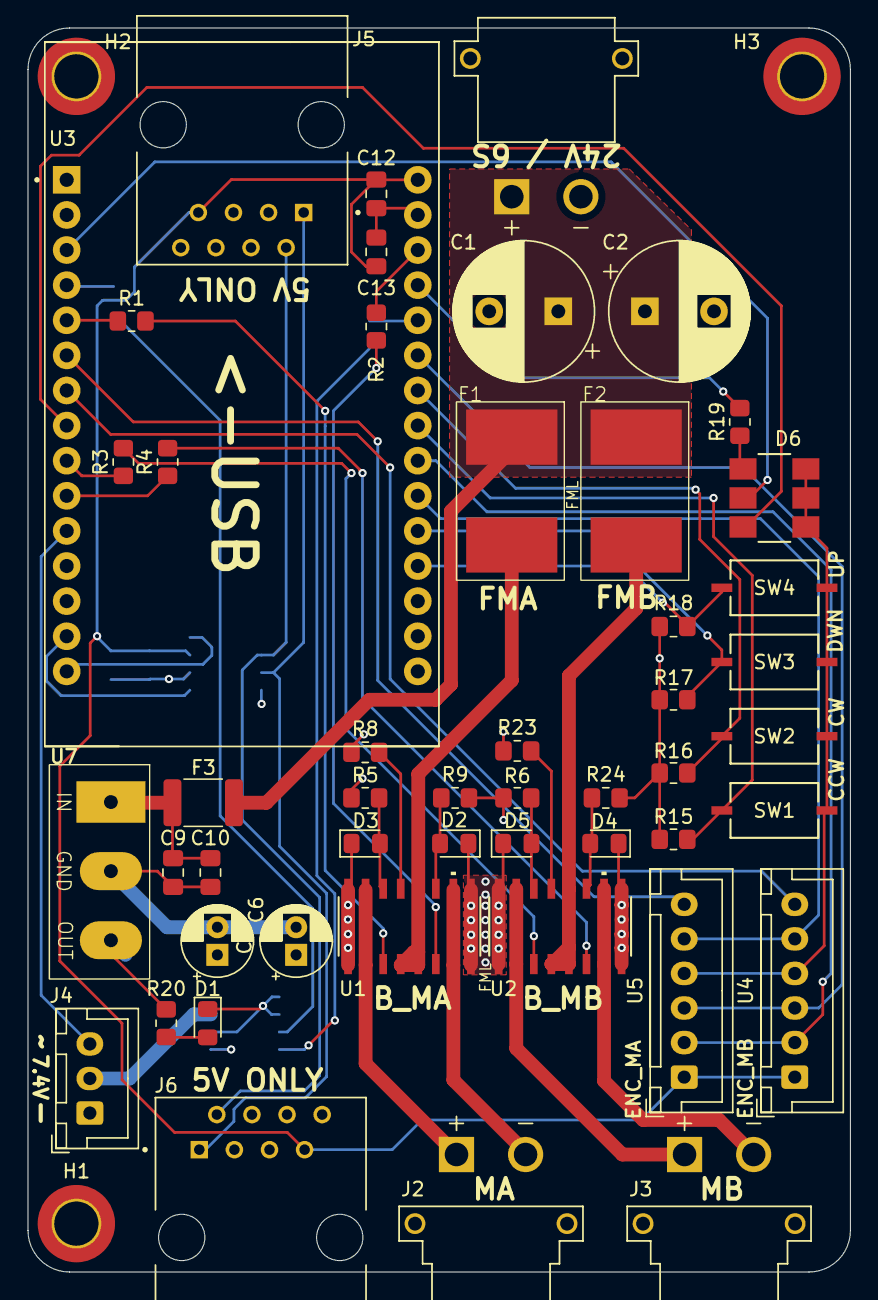
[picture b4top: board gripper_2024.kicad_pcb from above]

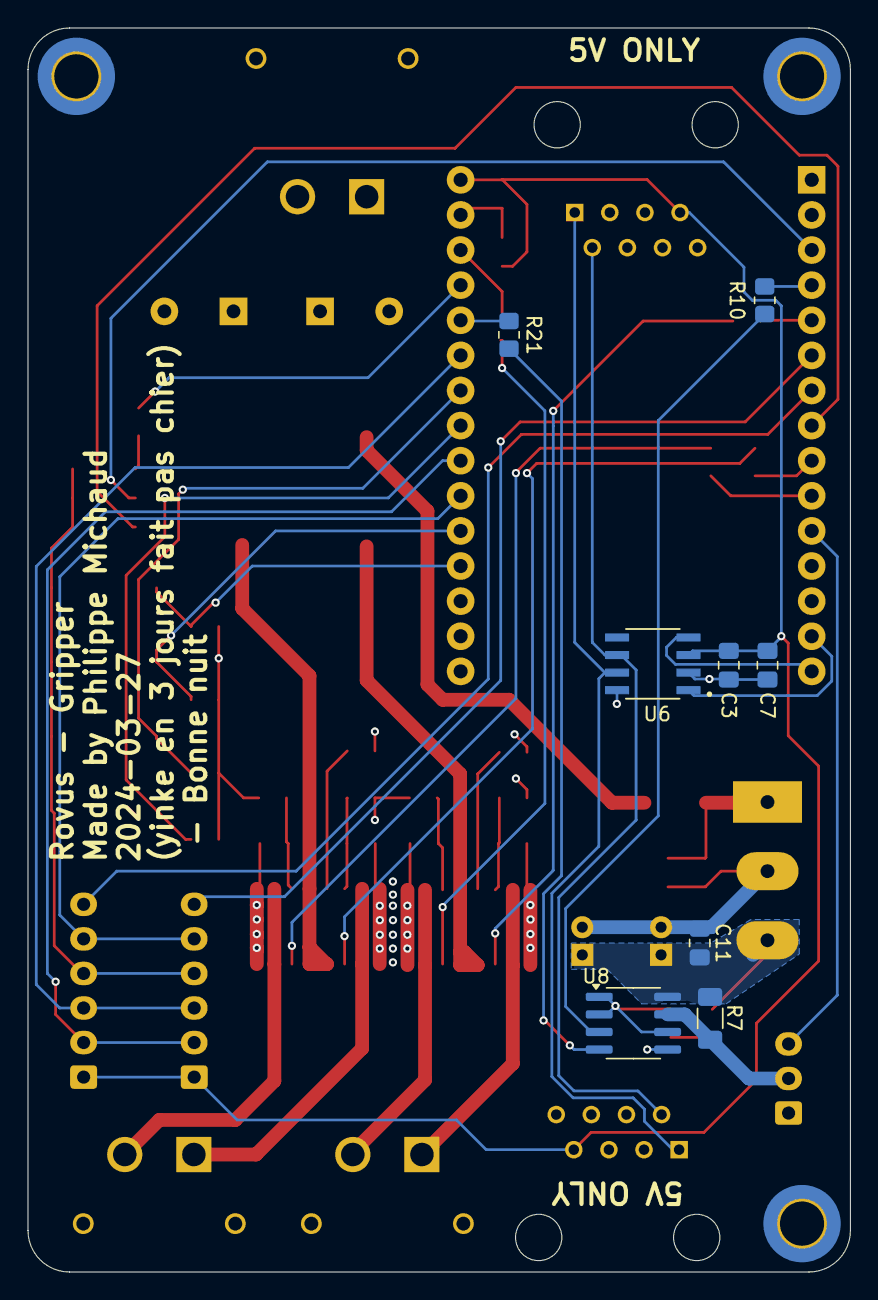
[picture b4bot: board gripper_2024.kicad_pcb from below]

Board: 4 copper layers, 59.5 x 90.0 mm, 60 parts (8 on the bottom side), 50 nets.

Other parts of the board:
D6: CLP6C-FKB-CKNPRGJBB7A363; CLP6C-FKB-CKNPRGJBB7A363_CRE

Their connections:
GND: D6.4, D6.5, D6.6; also elsewhere on the board
LED_B: D6.3; also elsewhere on the board
LED_G: D6.2; also elsewhere on the board
unnamed 29: D6.1; also elsewhere on the board
